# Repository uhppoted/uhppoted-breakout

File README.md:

# uhppoted-breakout

Breakout board for the UHPPOTE TCP/IP Wiegand 26 access controllers. 

The breakout board substitutes the removable CPU board with a hackable board that:
- Exposes the interface connector pins as a pair of standard 2.54mm (0.1") headers
- Serialises card swipes and I/O events out to an SPI interface
- Has mounting holes for an external CPU to do the heavy lifting (e.g. _RaspberryPi_ _Zero2W_)
- Includes an onboard RTC

## Raison d'être

Mostly curiosity? But .. it also opens up the possibility of:
- IPv6
- TLS
- UDP multicast
- onboard WiFi
- interfacing with off brand readers and keypads
- custom access control requirements

## Roadmap

### Rev.0

**IN DEVELOPMENT**

Initial proof of concept, designed to be relatively easy to hand solder and debug:
- All the components are on the front (top) of the PCB
- It uses the ever-so-cute _WaveShare_ _RP2040-Tiny_ module
- Through-hole components where convenient

#### Errata
1. Requires Schottky barrier diode and resistor on RX8900SA backup battery.
2. Add-on mounting holes are for RaspberryPi Pico.

## Notes

### Footprints
1. The silkscreen footprint for J10 and J12 on the CPU board of the controller is either mirrored or
   using the footprint for a pin header (presumably because the pin and socket headers were swapped for
   easier assembly and the silkscreen was never updated).

2. The silkscreen footprint for J10 and J11 on the base board of the controller is either mirrored or
   using the footprint for a pin socket (presumably because the pin and socket headers were swapped for
   easier assembly and the silkscreen was never updated).

3. The breakout board uses the correct footprints for the J10 and J12 socket headers that connect the
   board to the base board.

## License

Hardware is licensed under the CERN-OHL-S-2.0-S license, software is licensed under the MIT license.

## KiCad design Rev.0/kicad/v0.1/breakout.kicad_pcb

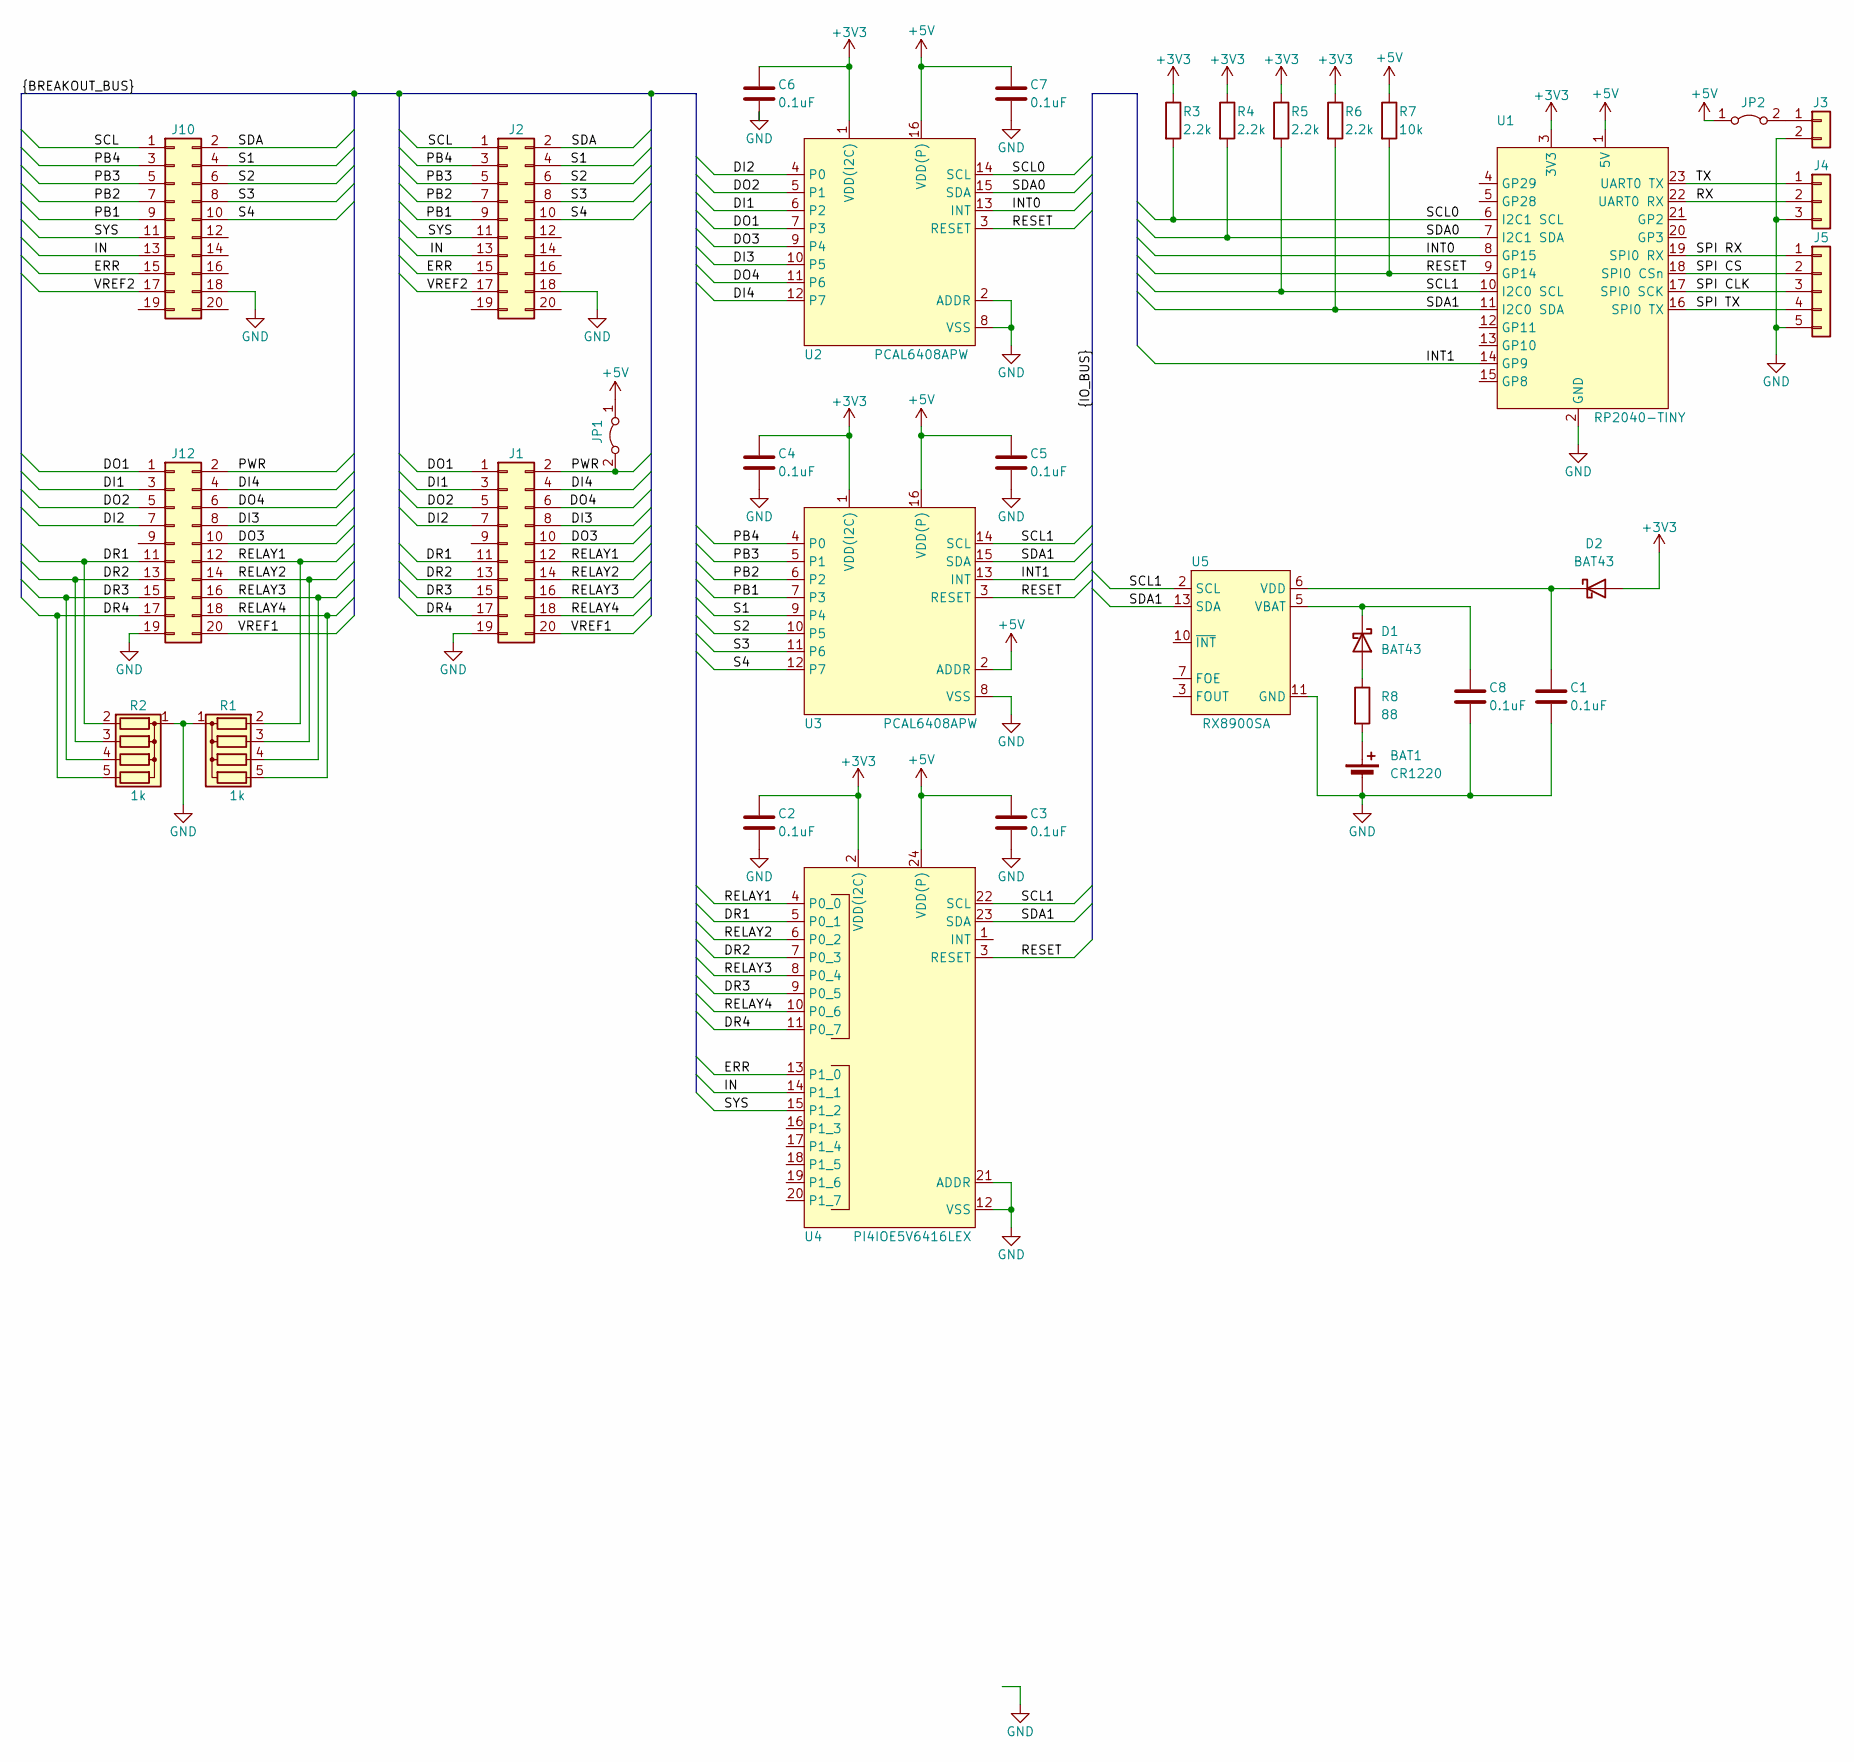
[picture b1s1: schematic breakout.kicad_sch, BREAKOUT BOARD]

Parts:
BAT1: CR1220; BatteryHolder_Keystone_3000_1x12mm
C1, C2, C3, C4, C5, C6, C7, C8: 0.1uF; C_0805_2012Metric_Pad1.18x1.45mm_HandSolder
D1, D2: BAT43; D_SOD-123
J1, J2: Conn_02x10_Odd_Even; PinHeader_2x10_P2.54mm_Vertical
J3: Conn_01x02; Molex_SPOX_5267-02A_1x02_P2.50mm_Vertical
J4: Conn_01x03_Pin; Molex_SPOX_5267-03A_1x03_P2.50mm_Vertical
J5: Conn_01x05_Pin; Molex_SPOX_5267-05A_1x05_P2.50mm_Vertical
J10, J12: Conn_02x10_Odd_Even; PinSocket_2x10_P2.00mm_Vertical
JP1, JP2: Jumper_2_Bridged; PinHeader_1x02_P2.54mm_Vertical
R1, R2: 1k; R_Array_SIP5
R3, R4, R5, R6: 2.2k; R_Axial_DIN0207_L6.3mm_D2.5mm_P10.16mm_Horizontal
R7: 10k; R_Axial_DIN0207_L6.3mm_D2.5mm_P10.16mm_Horizontal
R8: 88; R_1206_3216Metric_Pad1.30x1.75mm_HandSolder
U1: RP2040-TINY
U2, U3: PCAL6408APW; TSSOP-16_4.4x5mm_P0.65mm
U4: PI4IOE5V6416LEX; TSSOP-24_4.4x7.8mm_P0.65mm
U5: RX8900SA

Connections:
+3V3: C2.1, C4.1, C6.1, D2.2 (A), R3.1, R4.1, R5.1, R6.1, U1.3 (3V3), U2.1 (VDD(I2C)), U3.1 (VDD(I2C)), U4.2 (VDD(I2C))
+5V: C3.1, C5.1, C7.1, JP1.1 (A), JP2.1 (A), R7.1, U1.1 (5V), U2.16 (VDD(P)), U3.2 (ADDR), U3.16 (VDD(P)), U4.24 (VDD(P))
/DI1: J1.3, J12.3, U2.6 (P2)
/DI2: J1.7, J12.7, U2.4 (P0)
/DI3: J1.8, J12.8, U2.10 (P5)
/DI4: J1.4, J12.4, U2.12 (P7)
/DO1: J1.1, J12.1, U2.7 (P3)
/DO2: J1.5, J12.5, U2.5 (P1)
/DO3: J1.10, J12.10, U2.9 (P4)
/DO4: J1.6, J12.6, U2.11 (P6)
/DR1: J1.11, J12.11, R2.2 (R1), U4.5 (P0_1)
/DR2: J1.13, J12.13, R2.3 (R2), U4.7 (P0_3)
/DR3: J1.15, J12.15, R2.4 (R3), U4.9 (P0_5)
/DR4: J1.17, J12.17, R2.5 (R4), U4.11 (P0_7)
/ERR: J2.15, J10.15, U4.13 (P1_0)
/IN: J2.13, J10.13, U4.14 (P1_1)
/INT0: U1.8 (GP15), U2.13 (INT)
/INT1: U1.14 (GP9), U3.13 (INT)
/PB1: J2.9, J10.9, U3.7 (P3)
/PB2: J2.7, J10.7, U3.6 (P2)
/PB3: J2.5, J10.5, U3.5 (P1)
/PB4: J2.3, J10.3, U3.4 (P0)
/PWR: J1.2, J12.2, JP1.2 (B)
/RELAY1: J1.12, J12.12, R1.2 (R1), U4.4 (P0_0)
/RELAY2: J1.14, J12.14, R1.3 (R2), U4.6 (P0_2)
/RELAY3: J1.16, J12.16, R1.4 (R3), U4.8 (P0_4)
/RELAY4: J1.18, J12.18, R1.5 (R4), U4.10 (P0_6)
/RESET: R7.2, U1.9 (GP14), U2.3 (RESET), U3.3 (RESET), U4.3 (RESET)
/RX: J4.2, U1.22 (UART0 RX)
/S1: J2.4, J10.4, U3.9 (P4)
/S2: J2.6, J10.6, U3.10 (P5)
/S3: J2.8, J10.8, U3.11 (P6)
/S4: J2.10, J10.10, U3.12 (P7)
/SCL: J2.1, J10.1
/SCL0: R3.2, U1.6 (I2C1 SCL), U2.14 (SCL)
/SCL1: R5.2, U1.10 (I2C0 SCL), U3.14 (SCL), U4.22 (SCL), U5.2 (SCL)
/SDA: J2.2, J10.2
/SDA0: R4.2, U1.7 (I2C1 SDA), U2.15 (SDA)
/SDA1: R6.2, U1.11 (I2C0 SDA), U3.15 (SDA), U4.23 (SDA), U5.13 (SDA)
/SPI CLK: J5.3, U1.17 (SPI0 SCK)
/SPI CS: J5.2, U1.18 (SPI0 CSn)
/SPI RX: J5.1, U1.19 (SPI0 RX)
/SPI TX: J5.4, U1.16 (SPI0 TX)
/SYS: J2.11, J10.11, U4.15 (P1_2)
/TX: J4.1, U1.23 (UART0 TX)
/VREF1: J1.20, J12.20
/VREF2: J2.17, J10.17
GND: BAT1.2 (-), C1.2, C2.2, C3.2, C4.2, C5.2, C6.2, C7.2, C8.2, J1.19, J2.18, J3.2, J4.3, J5.5, J10.18, J12.19, R1.1 (common), R2.1 (common), U1.2 (GND), U2.2 (ADDR), U2.8 (VSS), U3.8 (VSS), U4.12 (VSS), U4.21 (ADDR), U5.11 (GND)
unnamed: BAT1.1 (+), R8.2
unnamed: D1.2 (A), R8.1
unnamed: C8.1, D1.1 (K), U5.5 (VBAT)
unnamed: C1.1, D2.1 (K), U5.6 (VDD)
unnamed: J3.1, JP2.2 (B)

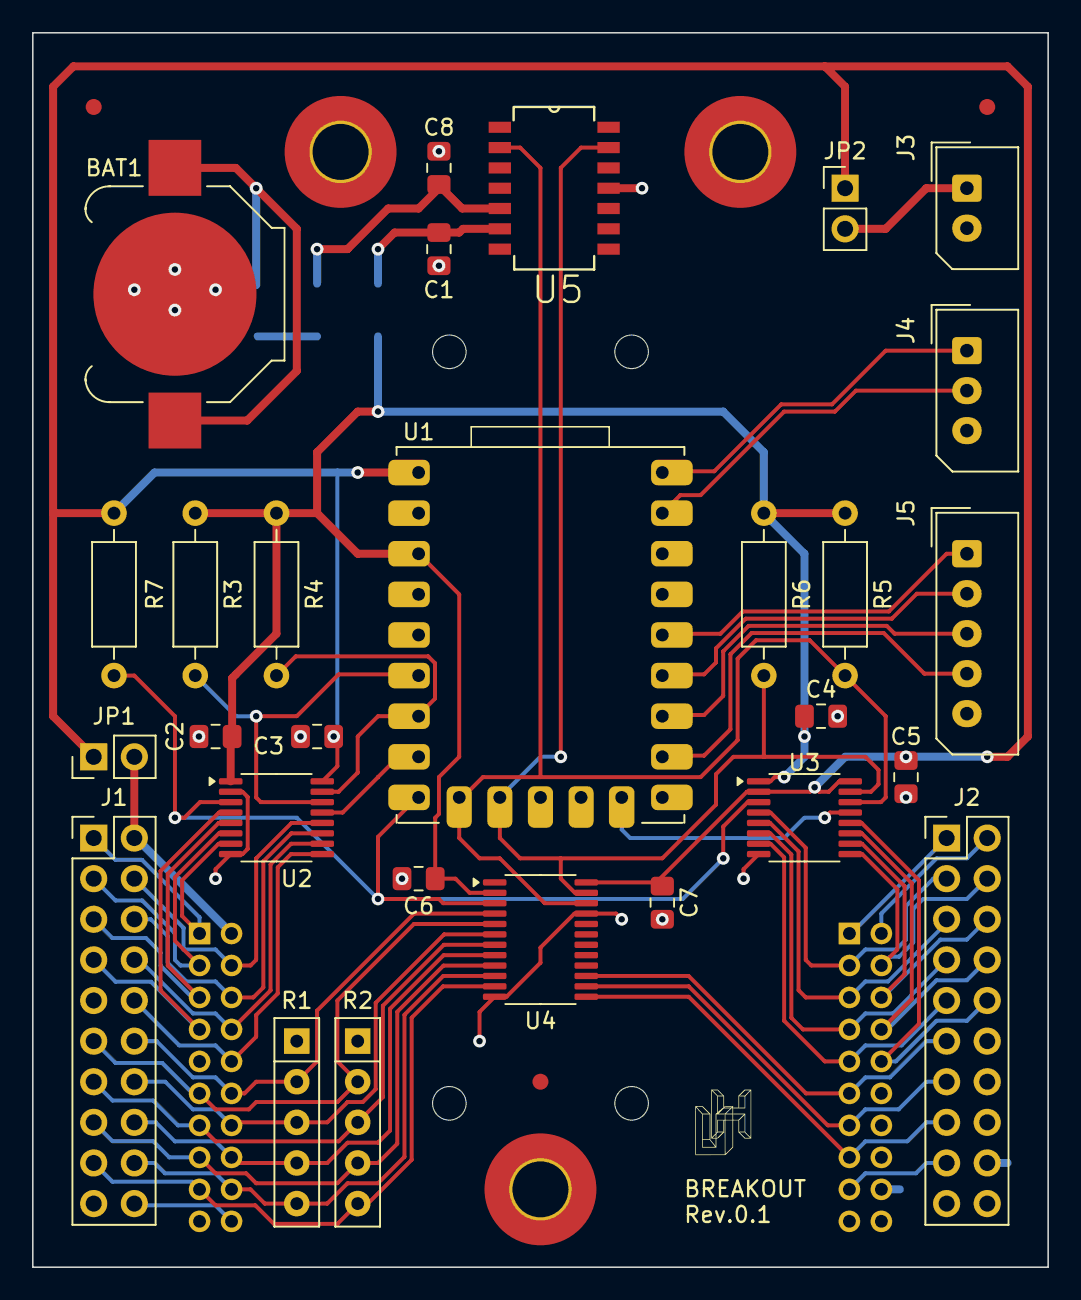
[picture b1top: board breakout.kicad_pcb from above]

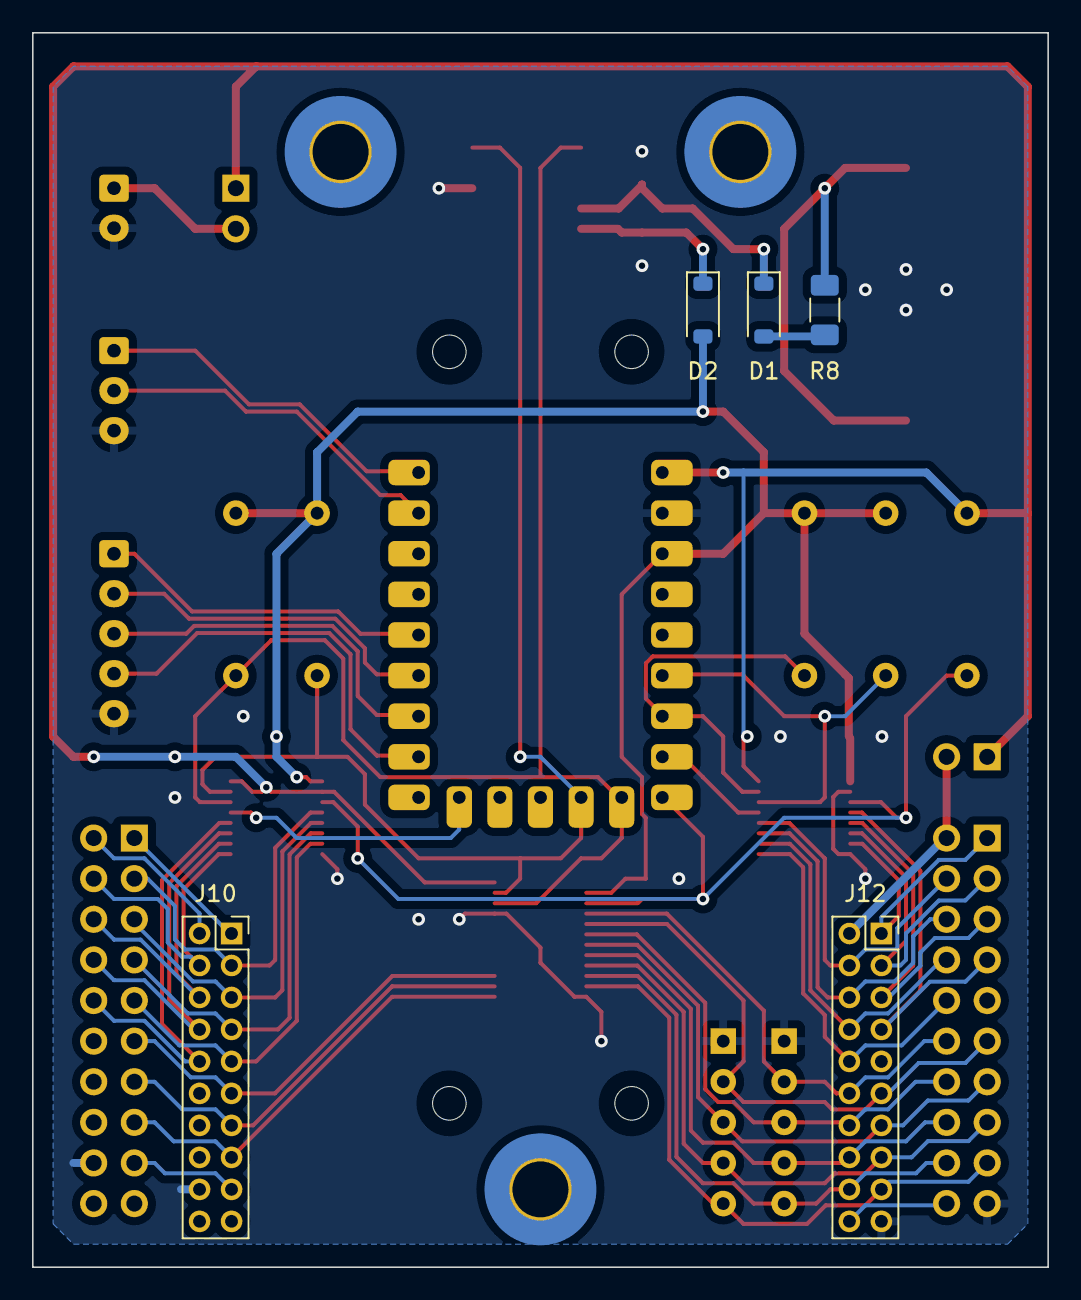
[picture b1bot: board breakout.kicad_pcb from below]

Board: 2 copper layers, 63.5 x 77.2 mm, 40 parts (5 on the bottom side), 53 nets.

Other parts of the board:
H1, H2, H3, H4: MountingHole_2.1mm
M1, M2, M2#2: MountingHole_3.5mm_Pad_TopBottom

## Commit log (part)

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2024-11-22 (interim commit) reproducible weirdosity - system tick stops working with with 'sequence' unpack
2024-11-22 Removed CLI timeout
2024-11-22 Reworked USB and UART to use circular buffer
2024-11-23 Removed SPI (unused)
2024-11-23 Added WATCHDOG to system errors and CMake build flags
2024-11-25 Moved 'on_tick' to core::sys
2024-11-25 Restructured Rev.0 Go emulator as a 'local only' package
2024-11-26 Restructuring Go emulator to use stub driver
2024-11-26 (debug) partially reinstated ASN.1 sequence unpack
2024-11-26 Removed calloc+free in print/println/_push
2024-11-26 (debugging) reinstating decoding for ASN.1 SEQUENCE
2024-11-27 Removed superfluous 'println' implementation
2024-11-28 Added MODE_NONE and MODE_LOG
2024-11-29 emulator: RPC driver skeleton
2024-12-03 Bump golang.org/x/sys in /Rev.0/logging/go
    Bumps [golang.org/x/sys](https://github.com/golang/sys) from 0.0.0-20200909081042-eff7692f9009 to 0.1.0.
    - [Commits](https://github.com/golang/sys/commits/v0.1.0)
    ---
    updated-dependencies:
    - dependency-name: golang.org/x/sys
    dependency-type: indirect
2024-12-04 Added mutex around print queue push/pop
2024-12-04 emulator: reworked 'get-controller' to use RPC
2024-12-06 (debug) added mutex around LED and checked SSMP message against 'expected' message
2024-12-06 emulator: CLI for testing/debugging
2024-12-07 driver: SSMP simulator skeleton
2024-12-07 breakout: cleaned up field allocation logic in ASN.1 decode
2024-12-09 (debug) printing timer info to stdout
2024-12-10 emulator: partial TLS support
2024-12-11 (debug) re-enabled RTC and SSMP PDU decoding
2024-12-11 emulator: get-time API function
2024-12-12 emulator: fixed TLS log tag
2024-12-12 emulator: set-time API function
2024-12-13 emulator: reworked config to use tempfile when updating
2024-12-13 (debug) reinstated U3 and partially decoded SSMP PDU
2024-12-14 (debug) reinstated U4
2024-12-15 (glitch) reinstated U4::init
2024-12-16 Fixed inverted 'memory error' flag in sys_healthcheck
2024-12-16 breakout: extracting SSMP GET request version and community fields
2024-12-17 emulator: genericized driver 'get'
2024-12-17 (glitch) reinstated U4::tick relays
2024-12-18 breakout: reinstated SSMP GET OID and authorized check
2024-12-19 emulator: commonalised all the get/set operations into SCMP
2024-12-19 (glitch) reinstated U4::tick LEDs
2024-12-19 emulator: split SCMP 'set' and 'get' interfaces
2024-12-20 breakout: SSMP GET MIB lookup
2024-12-20 (glitch) reinstated U4:tick health check
2024-12-20 emulator: cleaned up processing for indexed OIDs
2024-12-21 (glitch) U4::healthcheck - task skeleton
2024-12-21 (glitch) U4::healthcheck - temporarily commented out push
2024-12-22 (glitch) U4::healthcheck - (temporarily) calloc
2024-12-22 (glitch) U4::healthcheck - removed debugf
2024-12-24 (glitch) implemented watchdog trace
2024-12-27 (glitch) watchdog stacktrace
2024-12-27 emulator: added support for multiple requests on an established TCP/IP connection
2024-12-31 emulator: added support for multiple requests on an established TLS connection
2024-12-31 (glitch) add tracepoints for U4::tick calloc/free
2024-12-31 (glitch) added internal tracepoints to ASN.1::unpack
2024-12-31 (glitch) added build timestamp to trace
2024-12-31 (glitch) added internall trace-in/out to ASN.1::unpack_int
2025-01-01 (glitch) added trace-in/out around SSMP::receive free packet/vector
2025-01-01 (glitch) added internal trace-in/out to ASN.1::unpack_pdu
2025-01-01 (glitch) added internal trace-in/out to packet::free
2025-01-01 (MVB) initial build from 'glitch' branch
2025-01-01 (mvb) removed U2 from build
2025-01-01 (mvb) added notes to MVB.md
2025-01-02 Added notes re. malloc/free + interrupts
2025-01-02 emulator: set-door API function
2025-01-02 emulator: closing UDP listener gracefully
2025-01-02 (glitch) initial mempool implementation for U4
2025-01-04 (glitch) replaced U4 mempool with 'operations' pool
2025-01-06 breakout: added 'trace' implementation from glitch branch
2025-01-06 emulator: closing TLS listener gracefully
2025-01-08 emulator: implemented exponential backoff when reopening a listen socket
2025-01-08 emulator: implemented request rate limit
2025-01-09 emulator: limited number of concurrent TCP and TLS connections
2025-01-10 breakout: fixed allocs in ssmp_encode_get_response
2025-01-10 emulator: TCP/IP connection accept rate limit
2025-01-14 breakout: dynamically allocated mempool array
2025-01-14 breakout: reinstated SSMP reply
2025-01-15 emulator: put-card API function
2025-01-16 emulator: added support for Unix domain sockets
2025-01-16 breakout: added queue message for U2 card swipe
2025-01-17 emulator: delete-all-cards API function
2025-01-18 breakout: reworked RTC to use mempool
2025-01-18 Renamed 'emulator' to 'zero2w'
2025-01-18 Restructured folders to consolidate all Zero2W stuff
2025-01-18 Updated Makefile for restructured folders
2025-01-21 breakout: U4 operation_free implementation
2025-01-21 breakout: checked operation of U3 and U4 with mempool
2025-01-22 breakout: U2 - fixed keycode (to use code length arg)
2025-01-28 breakout: implemented U4::operation_alloc
2025-01-29 Updated reference to uhppoted-lib-python repository
2025-02-03 breakout: implemented RTC::datetime_alloc/free
2025-02-03 rpcd: restructured to queue requests
2025-02-05 rpcd: encoding SSMP GET request
2025-02-05 breakout: swipe_alloc/free
2025-02-06 CLI: updated to use uhppoted-lib-python v0.8.10
2025-02-06 rpcd: parsed OID string
2025-02-06 breakout: migrated core/cli.c to use queue::push
2025-02-08 breakout: migrated U2,U3,UART and USB to use queue::push
2025-02-08 rpcd: encoding GET request
2025-02-11 rpcd: restructuring 'stub' to take encoded packet
2025-02-13 rpcd: decoding GET request
2025-02-13 breakout: extended PICO_XOSC_STARTUP_DELAY_MULTIPLIER to 64 (cf. https://tinygo.org/docs/reference/microcontrollers/machine/waveshare-rp2040-zero)
2025-02-14 rpcd: decoded GET request
2025-02-19 rpcd: restructured SSMP stub to return GetResponse
2025-02-19 breakout: updated to Pico SDK 2.1.1
2025-02-20 rpcd: decoded GetResponse
2025-02-21 breakout: set drive levels for SYS, ERR and IN LEDs
2025-02-22 rpcd: reworked 'stub' to return bisync encoded response
2025-02-25 breakout: clear U4 healthcheck flag only on successful 'push'
2025-02-25 rpcd: restructured to handle replies asynchronously
2025-02-26 rpcd: housekeeping for 'pending' list
2025-02-26 rpcd: reworked SSMP:SET to use new stub implementation
2025-02-28 breakout: 'stub' implemenation for debugging RPCD
2025-03-05 breakout: tiny-usb implementation (partial/reboot)
2025-03-05 breakout: updated github workflow for tiny-uart
2025-03-07 breakout: enabled CLI for tiny-usb
2025-03-10 breakout: restructured to select serial/USB interface for SSMP
2025-03-11 breakout: looped USB write until done
2025-03-12 rpcd: exponential backoff for SSMP serial reconnect
2025-03-17 breakout: reverted SSMP version to uint16
2025-03-18 breakout: SSMP get-datetime
2025-03-20 breakout: SSMP set-datetime
2025-03-25 breakout: added GET/SET operation type to SSMP request authorisation
2025-03-27 breakout: SSMP get-status:syserror and get-status:sysinfo
2025-04-01 breakout: SSMP get-door-open
2025-04-02 breakout: precalculated MIB hash table
2025-04-02 breakout: SSMP get-tamper-detect and get-fire-alarm
2025-04-03 breakout: replacing hardcoded MIB lookup with table + hash lookup
2025-04-07 ut0311: mapped breakout errors to uint8 code
2025-04-07 Returned SSMP_ERROR_AUTHORIZATION for unauthorised GET/SET requests
2025-04-08 breakout: get/set-datetime RTC functions
2025-04-09 Reworked set-time to delay for 1ms and then return current RTC time
2025-04-09 breakout: reworked SSMP logic to prioritize NO_SUCH_OBJECT error over NO_ACCESS
2025-04-14 breakout: removed debugging to RP2040 RTC weirdness
2025-04-14 breakout: added delta check to MIB::set-datetime
2025-04-15 ut0311: tracking down queuing issue for get-status
2025-04-16 breakout: get-door-mode and get-door-delay
2025-04-16 rpcd: debugging infinite queue
2025-04-22 breakout: moved doors configuration to 'setttings'
2025-04-23 breakout: reinstated error message for syserror
2025-04-24 breakout: included all errors in CLI 'state' command
2025-04-28 breakout: reworked set_error to only log queue/memory/etc errors once
2025-04-29 breakout: reworked set_error to log every N errors
2025-04-30 breakout: reworked syserror with loggable interval
2025-04-30 rpcd: forwarding event trap
2025-05-01 breakout: added 'clear errors' to CLI
2025-05-01 ut0311: added event handling skeleton
2025-05-05 breakout: commonalised door get/set-mode/delay/unlocked/open
2025-05-05 ut0311: event handling skeleton
2025-05-06 breakout: imlemented CLI up-arrow to echo previous command
2025-05-07 breakout: encoding trap var
2025-05-08 rpcd: packaged trap vars into RPC event message
2025-05-12 breakout: (interim fix) set RTC µs on write to reduce delta
2025-05-12 ut0311: sqlite3 DB implementation skeleton
2025-05-14 breakout: reworked RTC to clear 'ready' after write
2025-05-14 ut0311: closed RPCD event listener on shutdown
2025-05-20 breakout: implemented Ki for RTC time synchronisation
2025-05-21 breakout: implemented Kd for RTC time synchronisation
2025-05-22 breakout: added anti-windup to RTC PID
2025-05-22 ut0311: moved caching from RPCD to UT0311
2025-05-26 breakout: wrapped up hardware timer RTC
2025-05-26 ut0311: preparing for rearchitecture
2025-05-28 eventd: initial import
2025-06-03 breakout: added guard to USB1 write
2025-06-03 eventd: migrated 'get-event-index' from ut0311
2025-06-03 ut0311: migrated get-status to use events RPC
2025-06-05 eventsd: added controller to 'events' table
2025-06-06 eventd: cleaned up sqlite3 logic
2025-06-10 breakout: added event traps for doors 2-4 open/close
2025-06-12 breakout: added event traps for door buttons pressed/released
2025-06-16 breakout: fixed watchdog enable
2025-06-17 rpcd: restructured main() for commands
2025-06-18 rpcd: set service command line args
2025-06-18 ut0311: extracting 'trap' to it's own file
2025-06-18 ut0311: reworking events to use state changes
2025-06-19 ut0311: restructured to generate events on state updates
2025-06-24 ut0311: state poll skeleton
2025-06-25 eventd: added modernc sqlite3 driver (CGO cross-compilation complications)
2025-06-26 ut0311: get status and event-status from ut0311.state
2025-07-23 (interim commit) dunno - just stuff
2025-08-06 (interim commit) card swipe trap
2025-08-07 breakout: fixed typo in card swipe event handling
2025-08-12 ut0311: removed unused 'db' package
2025-08-12 ut0311: separated events and cards RPC interfaces
2025-08-12 get-status: fetching door-open/button state from UT0311::state
2025-08-13 ut0311: 'put-card' stores card to sqlite DB
2025-08-18 ut0311: reworked get-cards to use DB
2025-08-19 ut0311: migrated delete-card to sqlite
2025-08-20 dbd: unified mattn:sqlite3 and modernc:sqlite driver implementations
2025-08-21 get-card-by-index: migrated to sqlite3
2025-08-21 MIB: removed card OIDs
2025-08-25 rpcd: reworked rpcd::set to use tag-value pairs
2025-08-26 dbd: fixed sqlite3 connection reuse
2025-08-27 swipe: (partial) deny: door normally closed
2025-08-28 dbd: added 'system' service
2025-09-03 breakout: implemented door interlock for SSMP
2025-09-09 breakout: saving settings to flash
2025-09-10 breakout: reworked settings::save to write to flash iff actually changed
2025-09-15 ut0311: added interlock to DB
2025-09-17 ut0311: antipassback (in progress)
2025-09-18 anti-passback: checking against 'swipes' table
2025-09-22 ut0311: updating system 'swipes' table
2025-09-25 ut0311: 'pending' list for card swipe+PIN
2025-09-29 breakout: SSMP keycode trap (in progress)
2025-10-01 ut0311: send 'denied' event on new card swipe while previous swipe is pending PIN
2025-10-06 ut0311: (in progress) resetting timer on keypress
2025-10-07 ut0311: accumulating keypresses for swipe+PIN
2025-10-07 debug: reading back all configuration info
2025-10-09 breakout: fixed shift logic in PCAL6416A reads
2025-10-09 ut0311: reworked set-time to use RPCD
2025-10-15 breakout: automatically appending '#' to 6 digit and 'timeout' keycodes
2025-10-29 breakout: reworked USB to use write buffer
2025-10-30 breakout: reverted to synchronous write for USB.1 (faster and simpler)
2025-11-21 Post release cleanup
